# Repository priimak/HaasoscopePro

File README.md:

## HaasoscopePro

### An Affordable 2 GHz 3.2 GS/s 12 bit open-source open-hardware expandable USB oscilloscope

### [Available on CrowdSupply](https://www.crowdsupply.com/andy-haas/haasoscope-pro)

### [Hackaday.io Page](https://hackaday.io/project/200773-haasoscope-pro)

#### Schematics in PDF: [haasoscope_pro_adc_fpga_board_schematics.pdf](adc%20board%2Fhaasoscope_pro_adc_fpga_board_schematics.pdf)

#### Routing image: [haasoscope_pro_adc_fpga_board_routing.png](adc%20board%2Fhaasoscope_pro_adc_fpga_board_routing.png)

#### Firmware overview: [firmware schematic.pdf](adc%20board%20firmware/schematic.pdf)

### Quick start (Windows/Mac/Linux)

1) Plug Haasoscope Pro into your computer via USB C
2) Download code and unzip it: https://github.com/drandyhaas/HaasoscopePro/archive/refs/heads/main.zip
3) Run **HaasoscopeProQt** in the <code>HaasoscopePro/software/dist/(OS)_HaasoscopeProQt</code> directory

### Tips

- If not enough power is supplied or issues happen during readout, plug in via a powered USB hub, a USB-A to C cable, or use an external 12V power adapter
- If the board is not found on Linux, use this udev rule and then plug it in: <code>sudo cp HaasoscopePro/software/ft245.rules /etc/udev/rules.d/</code>
- If you get an error like "qt.qpa.plugin: Could not load the Qt platform plugin "xcb" in "" even though it was found", try: <code>sudo apt install libxcb-xinerama0</code>

### Fuller way of running

1) Install python3 and git (operating system dependent)
2) Install dependencies: <br><code>pip3 install numpy scipy pyqtgraph PyQt5 pyftdi ftd2xx</code>
3) Get code: <br><code>git clone https://github.com/drandyhaas/HaasoscopePro.git</code>
4) Install [FTDI D2xx driver](https://ftdichip.com/drivers/d2xx-drivers/)
<br>for Windows: install using the [setup exe](https://ftdichip.com/wp-content/uploads/2021/08/CDM212364_Setup.zip)
<br>for Mac can just do: <code>sudo cp HaasoscopePro/software/libftd2xx.dylib /usr/local/lib/</code> 
<br>for Linux can just do: <code>sudo cp HaasoscopePro/software/libftd2xx.so /usr/lib/</code>
5) Run:
<br><code>cd HaasoscopePro/software</code>
<br><code>python3 HaasoscopeProQt.py</code>
6) To remake exe for quick start:
<br><code>pip3 install pyinstaller</code> # install dependency once
<br><code>python3 -m PyInstaller HaasoscopeProQt.py</code>
<br><code>mv dist/HaasoscopeProQt dist/(OS)_HaasoscopeProQt</code>

### Repository structure

- [adc board](adc%20board/): Design files and documentation for the main board, based on Eagle 9.6.2
- [adc board/Kicad](adc%20board/Kicad): An import of the main board design files into KiCad 8
- [adc board firmware](adc%20board%20firmware/): Quartus lite project for the Altera Cyclone IV FPGA firmware (see [README](adc%20board%20firmware/README.md) in there for firmware upload instructions)
- [case](case/): Front and back PCB panels for the aluminum case
- [software](software/): Python files for the oscilloscope program
- [sub boards](sub%20boards/): Eagle design files and documentation for smaller test boards that were used during development 

### 2 GHz Active Probe

All designs for the accompanying active probe are in a separate [repository](https://github.com/drandyhaas/oshw-active-probe)

### Editing the GUI

The Haasoscope Pro GUI can be edited using [Qt Designer](https://www.pythonguis.com/installation/install-qt-designer-standalone/), started with:
<br><code>pip install pyqt5-tools</code>
<br><code>pyqt5-tools designer</code>
<br>Then open software/HaasoscopePro.ui or HaasoscopeProFFT.ui etc.

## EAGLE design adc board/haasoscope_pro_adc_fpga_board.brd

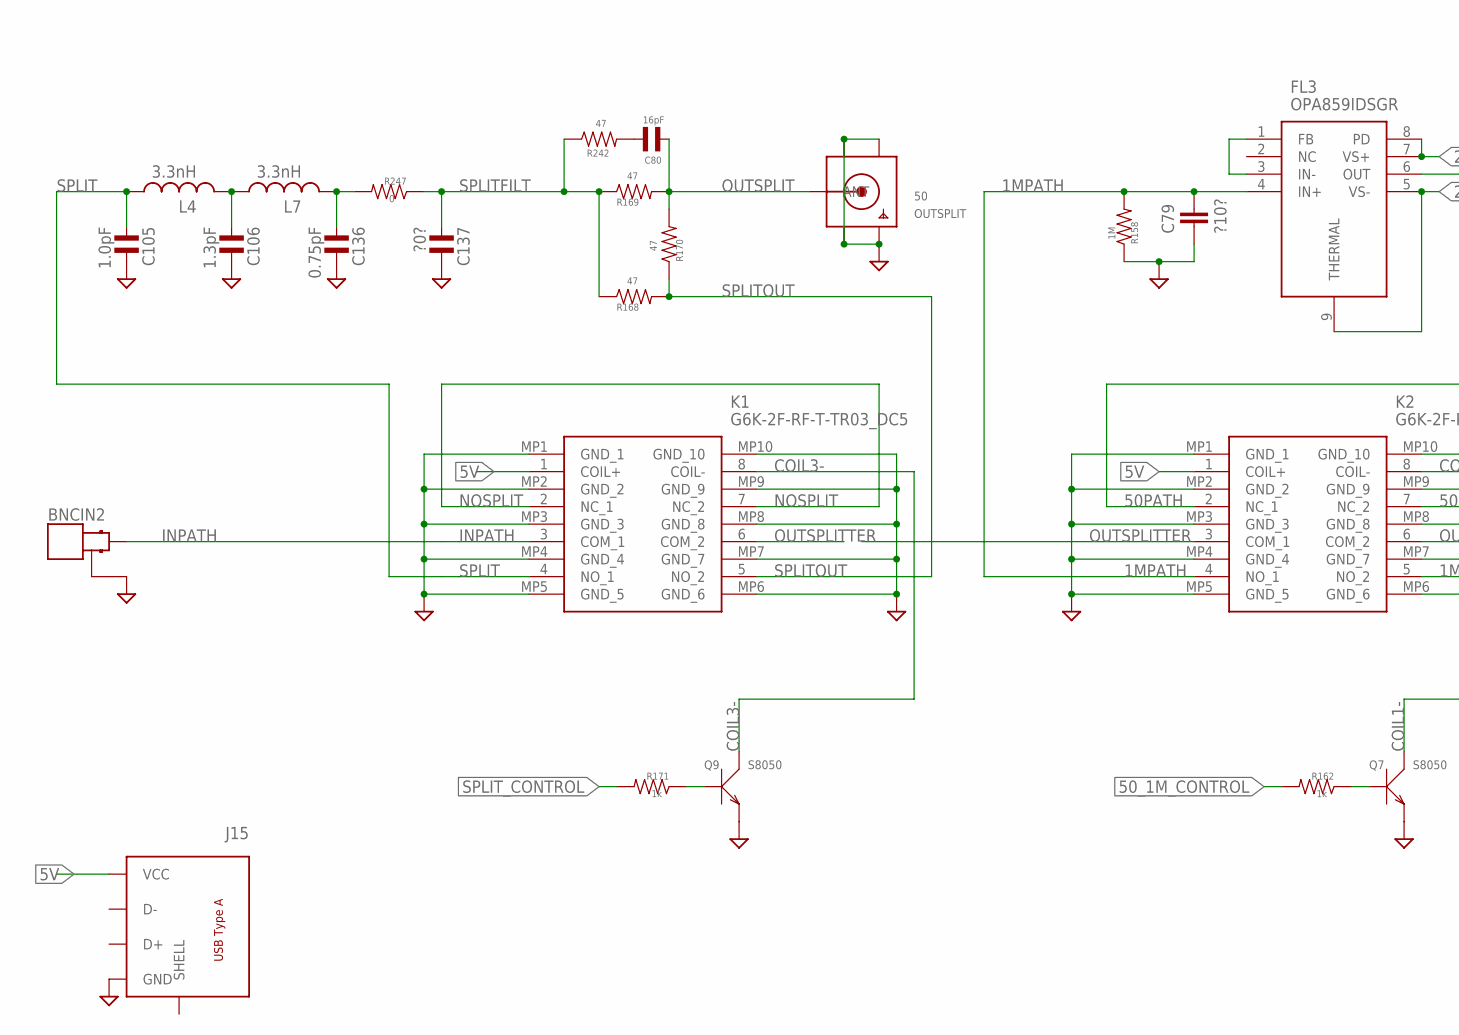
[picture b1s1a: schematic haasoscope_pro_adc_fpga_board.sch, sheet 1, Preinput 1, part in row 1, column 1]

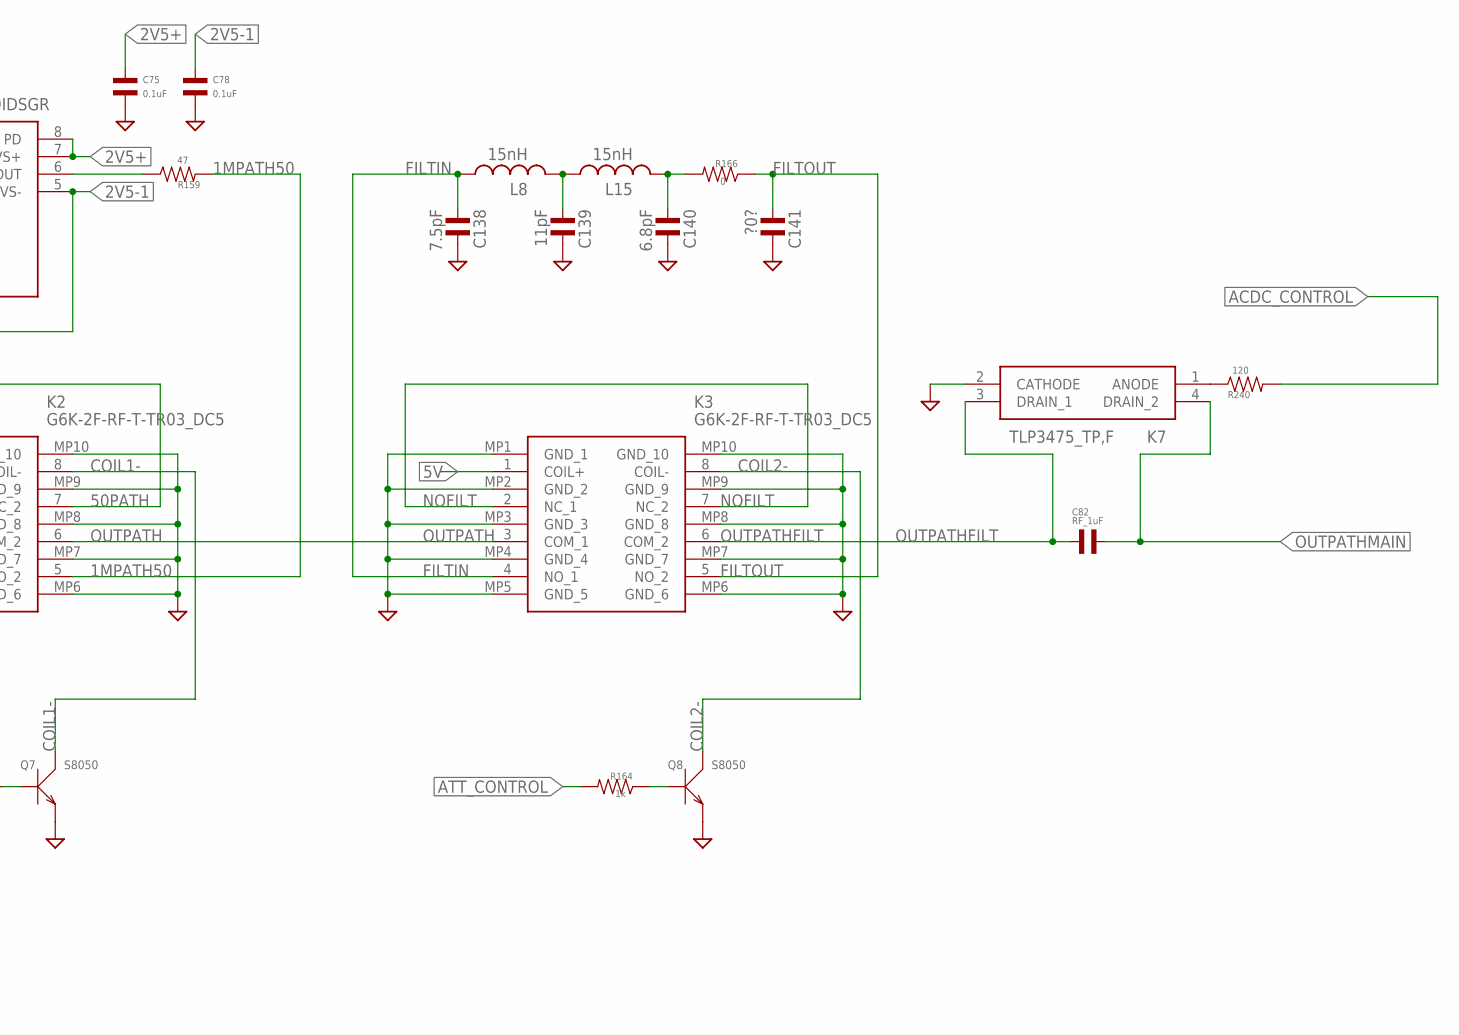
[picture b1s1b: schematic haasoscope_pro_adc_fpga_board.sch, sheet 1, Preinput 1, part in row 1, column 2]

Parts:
BNCIN2: MOLEX_BNC_73100-0105; MOLEX-BNC-73100-0105; MPN 73100-0105
C75, C78: 0.1uF; C0402
C79: ?10?; C0805
C80: 16pF; C0402
C82: RF_1uF; C0402; LCSC C52923
C105: 1.0pF; C0402
C106: 1.3pF; C0402
C136: 0.75pF; C0402
C137, C141: ?0?; C0402
C138: 7.5pF; C0402
C139: 11pF; C0402
C140: 6.8pF; C0402
FL3: OPA859IDSGR; SON50P200X200X80-9N
J15: test1; USB-2.0-A-THT-RA-TE_AMP-292303-1
K1, K2, K3: G6K-2F-RF-T-TR03_DC5; G6K2FRFTTR03DC5
K7: TLP3475_TP,F; TLP3475TPF; MANUFACTURER_PART_NUMBER TLP3475; MOUSER_PART_NUMBER 757-TLP3475
L4, L7: 3.3nH; RESC0402_N; LCSC C162542
L8, L15: 15nH; RESC0402_N; LCSC C521066
OUTSPLIT: 50; SMA_EDGELAUNCH
Q7, Q8, Q9: S8050; SOT-23; LCSC C7420370
R158: 1M; R0402
R159, R168, R169, R170, R242: 47; R0402
R162, R164, R171: 1k; R0402
R166, R247: 0; R0402
R240: 120; R0402

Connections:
1MPATH: C79.2, FL3.4 (IN+), K2.4 (NO_1), R158.P$2
1MPATH50: K2.5 (NO_2), R159.P$2
2V5+: C75.P$1, FL3.7 (VS+), FL3.8 (PD); also elsewhere on the board
2V5-1: C78.P$1, FL3.5 (VS-), FL3.9 (THERMAL); also elsewhere on the board
5V: J15.P$1 (VCC), K1.1 (COIL+), K2.1 (COIL+), K3.1 (COIL+); also elsewhere on the board
50PATH: K2.2 (NC_1), K2.7 (NC_2)
50_1M_CONTROL: R162.P$2; also elsewhere on the board
ACDC_CONTROL: R240.P$2; also elsewhere on the board
ATT_CONTROL: R164.P$2; also elsewhere on the board
COIL1-: K2.8 (COIL-), Q7.3 (C)
COIL2-: K3.8 (COIL-), Q8.3 (C)
COIL3-: K1.8 (COIL-), Q9.3 (C)
FILTIN: C138.P$1, K3.4 (NO_1), L8.1
FILTOUT: C141.P$1, K3.5 (NO_2), R166.P$1
GND: BNCIN2.GND1 (GND), BNCIN2.GND2 (GND), C75.P$2, C78.P$2, C79.1, C105.P$2, C106.P$2, C136.P$2, C137.P$2, C138.P$2, C139.P$2, C140.P$2, C141.P$2, J15.P$4 (GND), K1.MP1 (GND_1), K1.MP2 (GND_2), K1.MP3 (GND_3), K1.MP4 (GND_4), K1.MP5 (GND_5), K1.MP6 (GND_6), K1.MP7 (GND_7), K1.MP8 (GND_8), K1.MP9 (GND_9), K1.MP10 (GND_10), K2.MP1 (GND_1), K2.MP2 (GND_2), K2.MP3 (GND_3), K2.MP4 (GND_4), K2.MP5 (GND_5), K2.MP6 (GND_6), K2.MP7 (GND_7), K2.MP8 (GND_8), K2.MP9 (GND_9), K2.MP10 (GND_10), K3.MP1 (GND_1), K3.MP2 (GND_2), K3.MP3 (GND_3), K3.MP4 (GND_4), K3.MP5 (GND_5), K3.MP6 (GND_6), K3.MP7 (GND_7), K3.MP8 (GND_8), K3.MP9 (GND_9), K3.MP10 (GND_10), K7.2 (CATHODE), OUTSPLIT.GND@1 (GND4), OUTSPLIT.GND@2 (GND3), OUTSPLIT.GND@3 (GND2), OUTSPLIT.GND@4 (GND1), Q7.2 (E), Q8.2 (E), Q9.2 (E), R158.P$1; also elsewhere on the board
INPATH: BNCIN2.SIGNAL, K1.3 (COM_1)
unnamed: C139.P$1, L8.2, L15.1
unnamed: FL3.6 (OUT), R159.P$1
unnamed: FL3.1 (FB), FL3.3 (IN-)
unnamed: Q7.1 (B), R162.P$1
unnamed: Q8.1 (B), R164.P$1
unnamed: Q9.1 (B), R171.P$1
unnamed: K7.1 (ANODE), R240.P$1
unnamed: C80.P$1, R242.P$2
unnamed: C140.P$1, L15.2, R166.P$2
unnamed: C136.P$1, L7.2, R247.P$2
unnamed: C106.P$1, L4.2, L7.1
NOFILT: K3.2 (NC_1), K3.7 (NC_2)
NOSPLIT: K1.2 (NC_1), K1.7 (NC_2)
OUTPATH: K2.6 (COM_2), K3.3 (COM_1)
OUTPATHFILT: C82.P$1, K3.6 (COM_2), K7.3 (DRAIN_1)
OUTPATHMAIN: C82.P$2, K7.4 (DRAIN_2); also elsewhere on the board
OUTSPLIT: C80.P$2, OUTSPLIT.P (ANT), R169.P$2, R170.P$2
OUTSPLITTER: K1.6 (COM_2), K2.3 (COM_1)
SPLIT: C105.P$1, K1.4 (NO_1), L4.1
SPLITFILT: C137.P$1, R168.P$1, R169.P$1, R242.P$1, R247.P$1
SPLITOUT: K1.5 (NO_2), R168.P$2, R170.P$1
SPLIT_CONTROL: R171.P$2; also elsewhere on the board

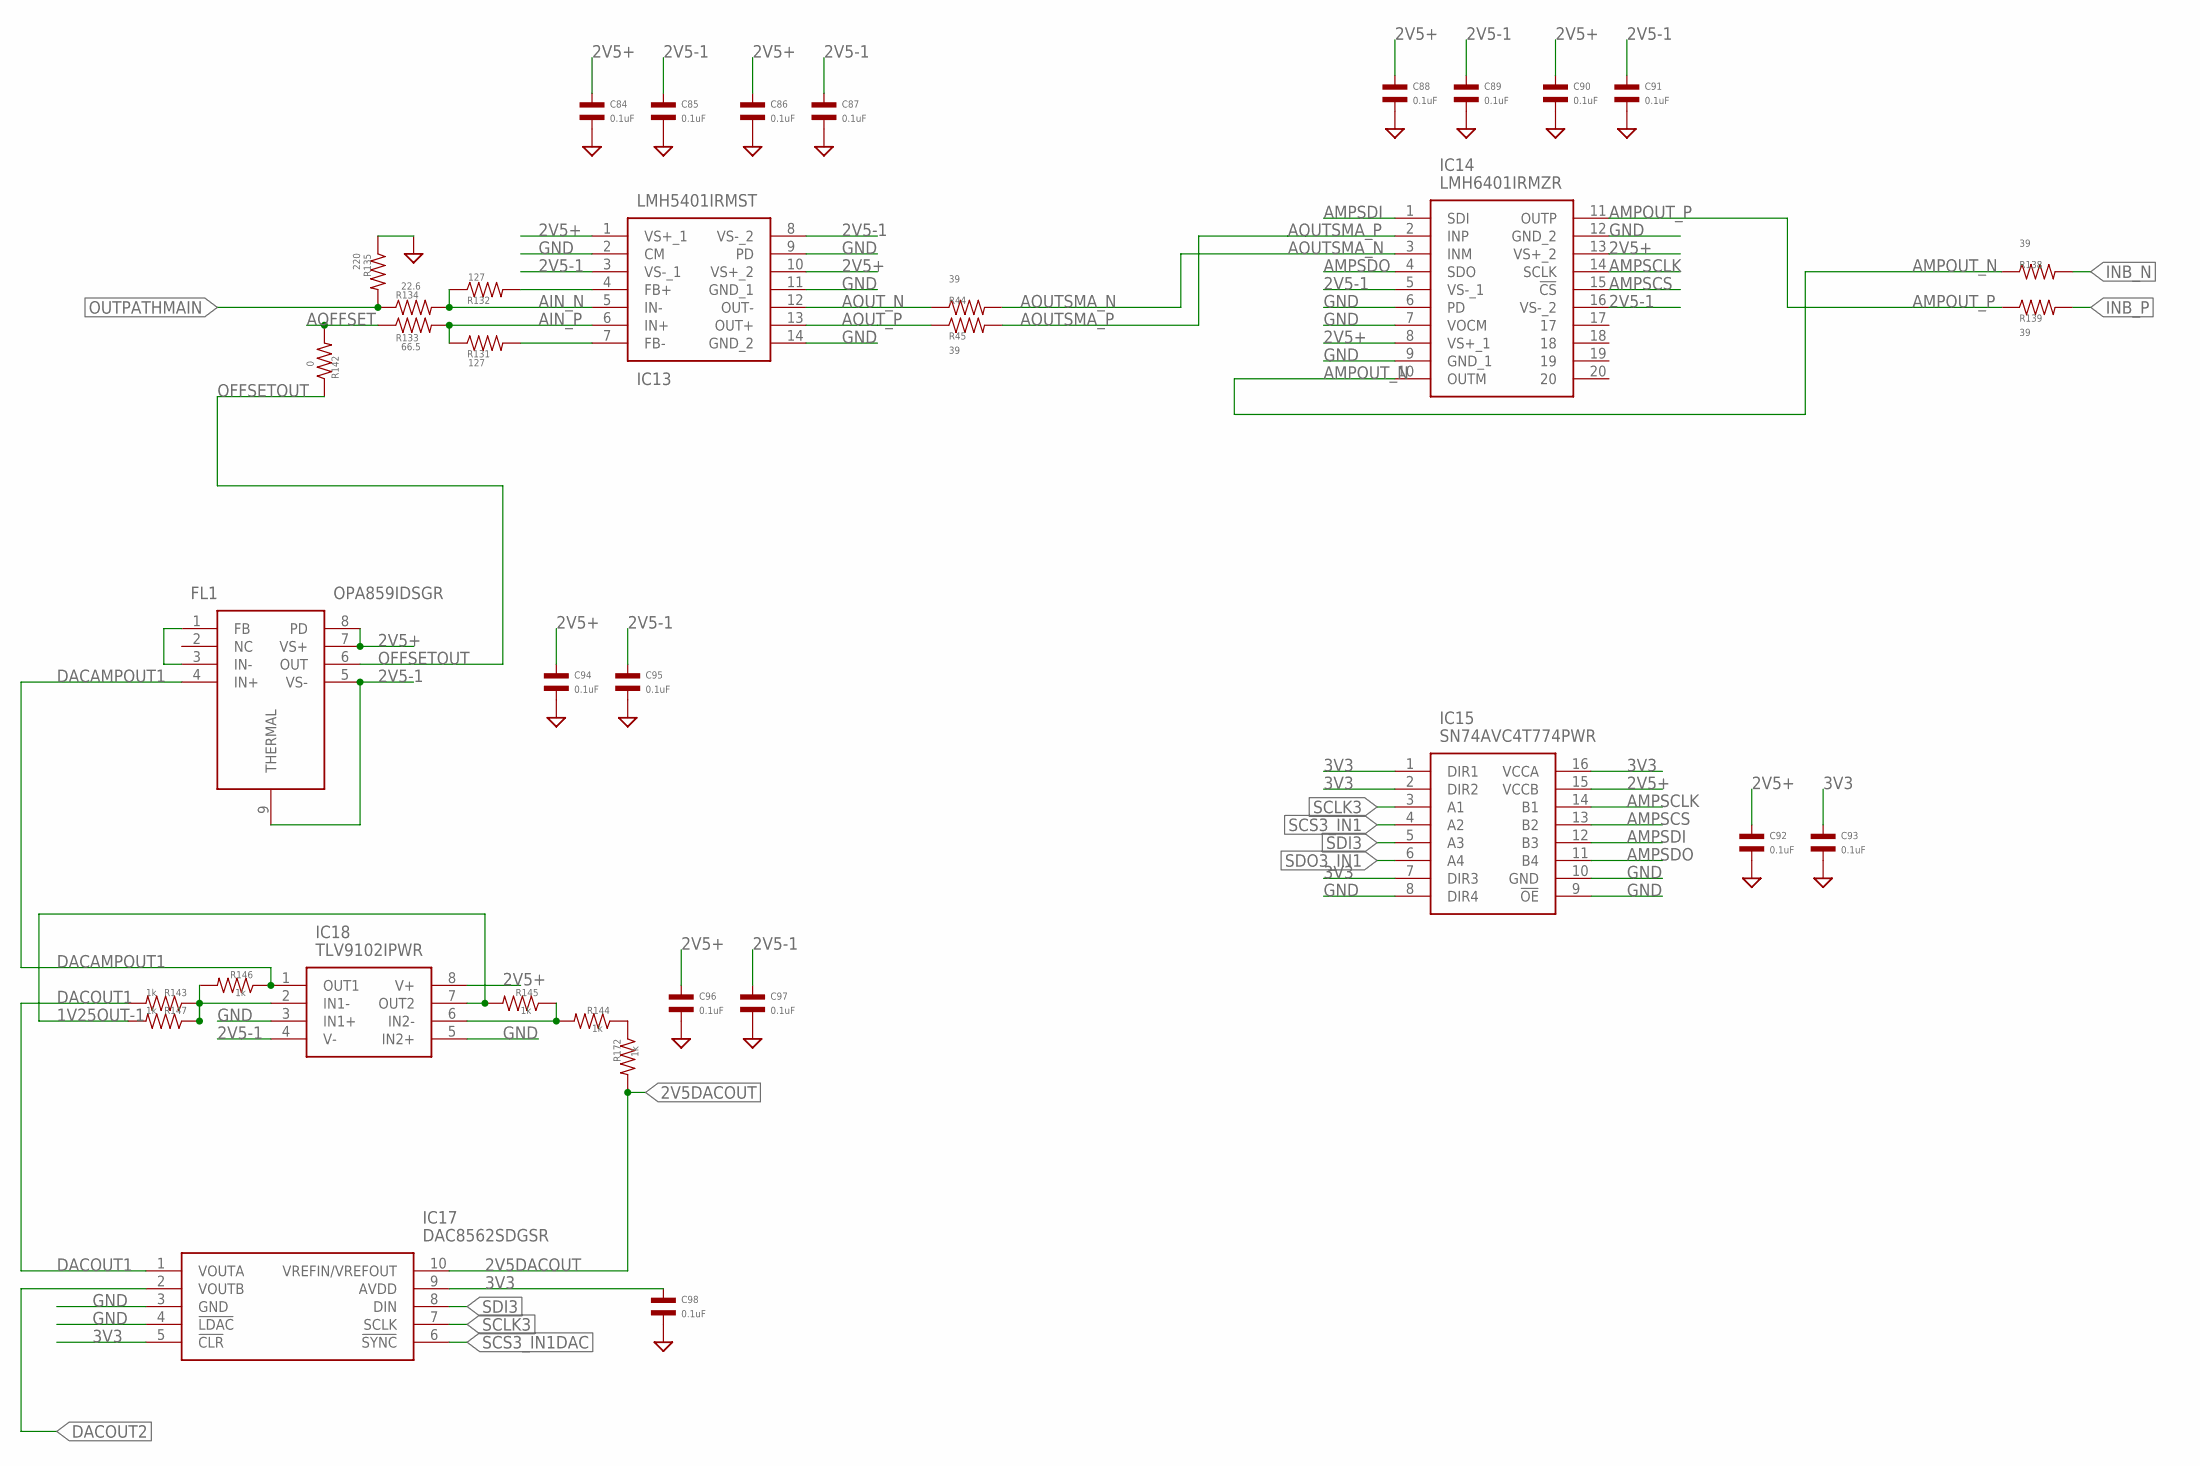
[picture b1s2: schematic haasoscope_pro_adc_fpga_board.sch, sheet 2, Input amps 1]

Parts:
C84, C85, C86, C87, C88, C89, C90, C91, C92, C93, C94, C95, C96, C97, C98: 0.1uF; C0402
FL1: OPA859IDSGR; SON50P200X200X80-9N
IC13: LMH5401IRMST; LMH5401IRMSR
IC14: LMH6401IRMZR
IC15: SN74AVC4T774PWR; SOP65P640X120-16N
IC17: DAC8562SDGSR; SOP50P490X110-10N
IC18: TLV9102IPWR; SOP65P640X120-8N
R44, R45, R138, R139: 39; R0402
R131, R132: 127; R0402
R133: 66.5; R0402
R134: 22.6; R0402
R135: 220; R0402
R142: 0; R0402
R143, R144, R145, R146, R147, R172: 1k; R0402

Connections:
1V25OUT-1: IC18.7 (OUT2), R145.P$2, R147.P$2
2V5+: C84.P$1, C86.P$1, C88.P$1, C90.P$1, C92.P$1, C94.P$1, C96.P$1, FL1.7 (VS+), FL1.8 (PD), IC13.1 (VS+_1), IC13.10 (VS+_2), IC14.8 (VS+_1), IC14.13 (VS+_2), IC15.15 (VCCB), IC18.8 (V+); also elsewhere on the board
2V5-1: C85.P$1, C87.P$1, C89.P$1, C91.P$1, C95.P$1, C97.P$1, FL1.5 (VS-), FL1.9 (THERMAL), IC13.3 (VS-_1), IC13.8 (VS-_2), IC14.5 (VS-_1), IC14.16 (VS-_2), IC18.4 (V-); also elsewhere on the board
2V5DACOUT: IC17.10 (VREFIN/VREFOUT), R172.P$2; also elsewhere on the board
3V3: C93.P$1, C98.P$1, IC15.1 (DIR1), IC15.2 (DIR2), IC15.7 (DIR3), IC15.16 (VCCA), IC17.5 (!CLR), IC17.9 (AVDD); also elsewhere on the board
AIN_N: IC13.5 (IN-), R132.P$1, R134.P$2
AIN_P: IC13.6 (IN+), R131.P$1, R133.P$2
AMPOUT_N: IC14.10 (OUTM), R138.P$1
AMPOUT_P: IC14.11 (OUTP), R139.P$1
AMPSCLK: IC14.14 (SCLK), IC15.14 (B1)
AMPSCS: IC14.15 (!CS), IC15.13 (B2)
AMPSDI: IC14.1 (SDI), IC15.12 (B3)
AMPSDO: IC14.4 (SDO), IC15.11 (B4)
AOFFSET: R133.P$1, R142.P$2
AOUTSMA_N: IC14.3 (INM), R44.P$2
AOUTSMA_P: IC14.2 (INP), R45.P$2
AOUT_N: IC13.12 (OUT-), R44.P$1
AOUT_P: IC13.13 (OUT+), R45.P$1
DACAMPOUT1: FL1.4 (IN+), IC18.1 (OUT1), R146.P$1
DACOUT1: IC17.1 (VOUTA), R143.P$2
DACOUT2: IC17.2 (VOUTB); also elsewhere on the board
GND: C84.P$2, C85.P$2, C86.P$2, C87.P$2, C88.P$2, C89.P$2, C90.P$2, C91.P$2, C92.P$2, C93.P$2, C94.P$2, C95.P$2, C96.P$2, C97.P$2, C98.P$2, IC13.2 (CM), IC13.9 (PD), IC13.11 (GND_1), IC13.14 (GND_2), IC14.6 (PD), IC14.7 (VOCM), IC14.9 (GND_1), IC14.12 (GND_2), IC15.8 (DIR4), IC15.9 (!OE), IC15.10 (GND), IC17.3 (GND), IC17.4 (!LDAC), IC18.3 (IN1+), IC18.5 (IN2+), R135.P$1; also elsewhere on the board
INB_N: R138.P$2; also elsewhere on the board
INB_P: R139.P$2; also elsewhere on the board
unnamed: FL1.1 (FB), FL1.3 (IN-)
unnamed: IC13.7 (FB-), R131.P$2
unnamed: IC13.4 (FB+), R132.P$2
unnamed: IC18.6 (IN2-), R144.P$2, R145.P$1
unnamed: IC18.2 (IN1-), R143.P$1, R146.P$2, R147.P$1
unnamed: R144.P$1, R172.P$1
OFFSETOUT: FL1.6 (OUT), R142.P$1
OUTPATHMAIN: R134.P$1, R135.P$2; also elsewhere on the board
SCLK3: IC15.3 (A1), IC17.7 (SCLK); also elsewhere on the board
SCS3_IN1: IC15.4 (A2); also elsewhere on the board
SCS3_IN1DAC: IC17.6 (!SYNC); also elsewhere on the board
SDI3: IC15.5 (A3), IC17.8 (DIN); also elsewhere on the board
SDO3_IN1: IC15.6 (A4); also elsewhere on the board

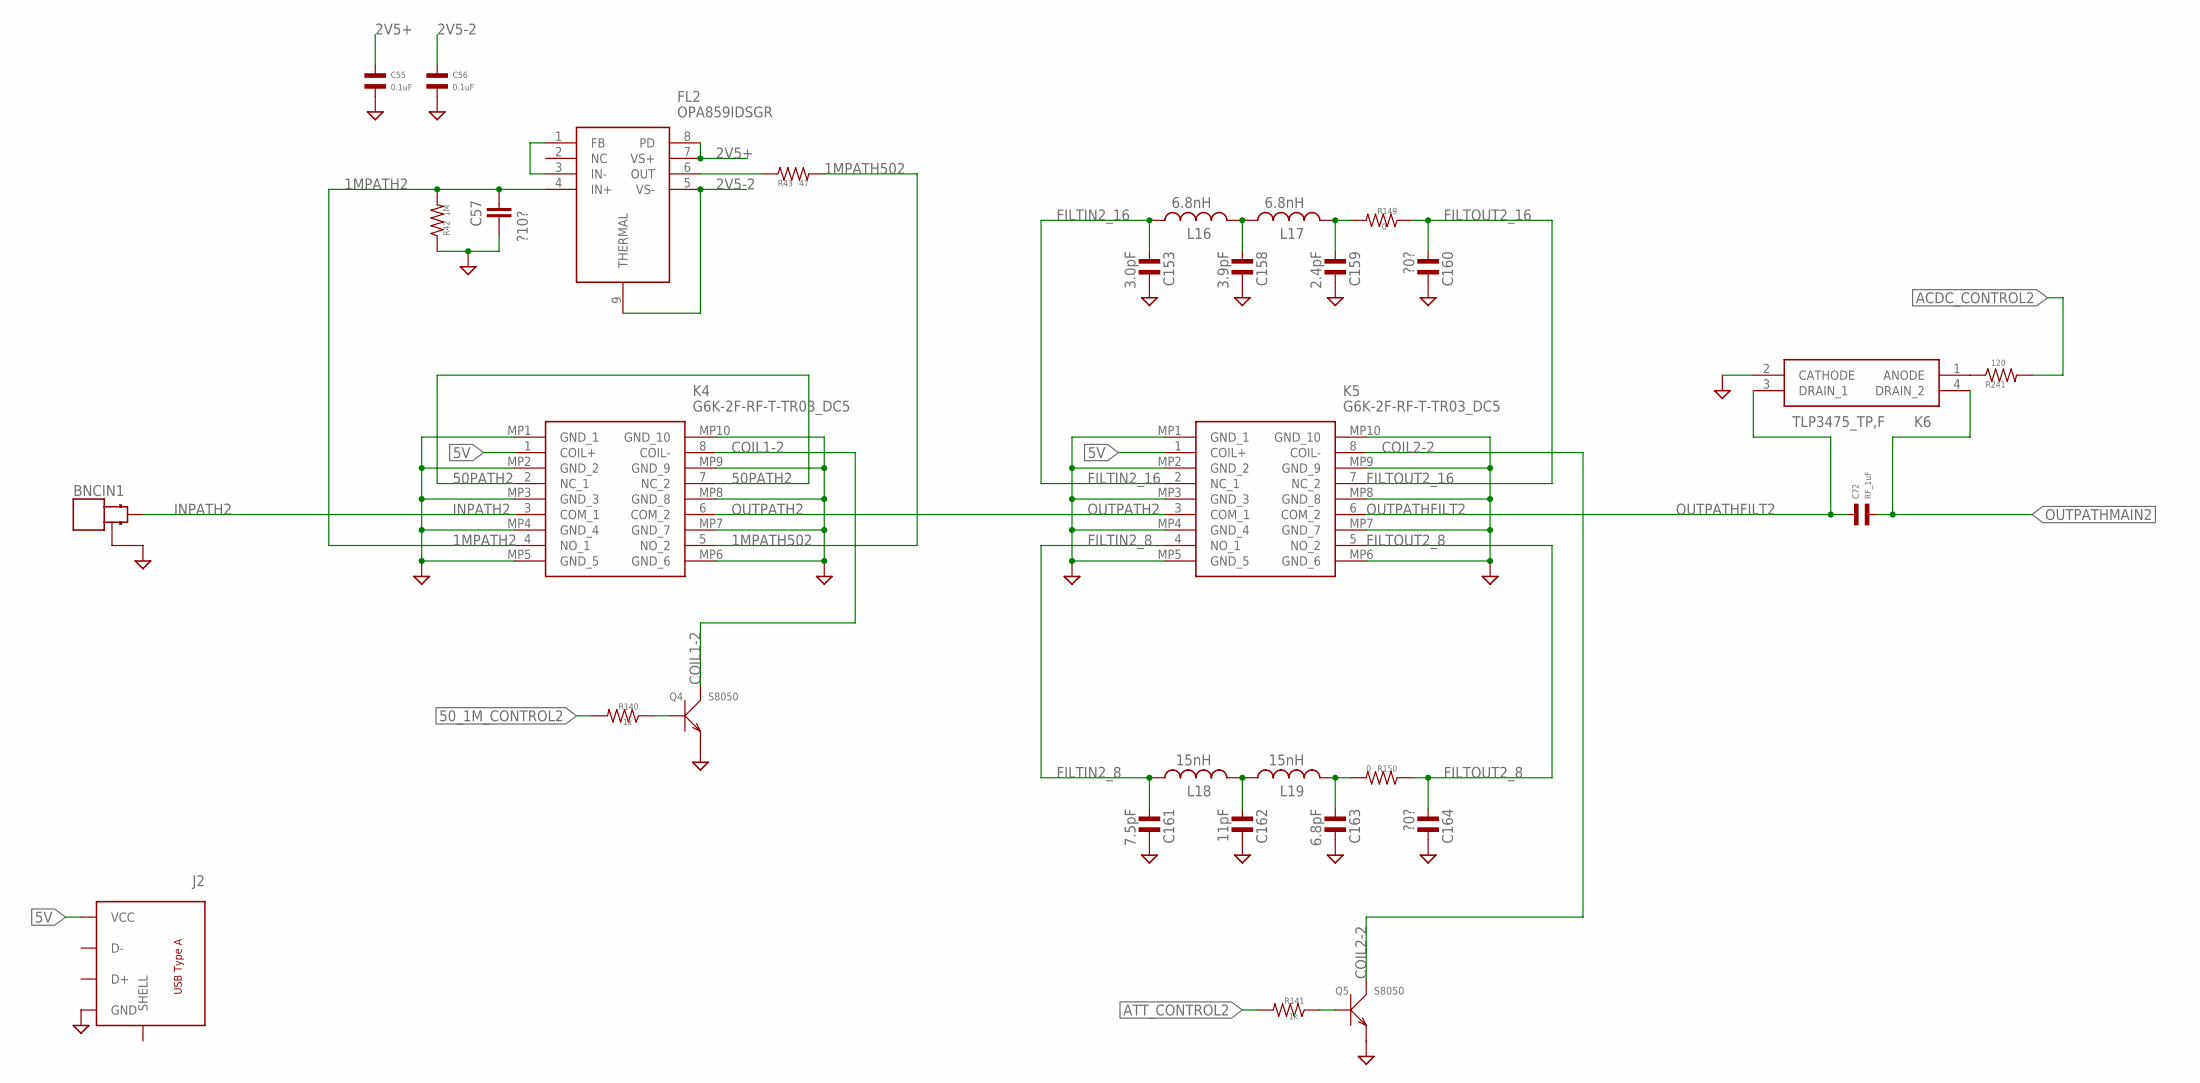
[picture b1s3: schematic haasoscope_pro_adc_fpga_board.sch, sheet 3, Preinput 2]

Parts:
BNCIN1: MOLEX_BNC_73100-0105; MOLEX-BNC-73100-0105; MPN 73100-0105
C55, C56: 0.1uF; C0402
C57: ?10?; C0805
C72: RF_1uF; C0402; LCSC C52923
C153: 3.0pF; C0402
C158: 3.9pF; C0402
C159: 2.4pF; C0402
C160, C164: ?0?; C0402
C161: 7.5pF; C0402
C162: 11pF; C0402
C163: 6.8pF; C0402
FL2: OPA859IDSGR; SON50P200X200X80-9N
J2: test1; USB-2.0-A-THT-RA-TE_AMP-292303-1
K4, K5: G6K-2F-RF-T-TR03_DC5; G6K2FRFTTR03DC5
K6: TLP3475_TP,F; TLP3475TPF; MANUFACTURER_PART_NUMBER TLP3475; MOUSER_PART_NUMBER 757-TLP3475
L16, L17: 6.8nH; RESC0402_N; LCSC C77110
L18, L19: 15nH; RESC0402_N; LCSC C521066
Q4, Q5: S8050; SOT-23; LCSC C7420370
R42: 1M; R0402
R43: 47; R0402
R140, R141: 1k; R0402
R149, R150: 0; R0402
R241: 120; R0402

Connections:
1MPATH2: C57.2, FL2.4 (IN+), K4.4 (NO_1), R42.P$2
1MPATH502: K4.5 (NO_2), R43.P$2
2V5+: C55.P$1, FL2.7 (VS+), FL2.8 (PD); also elsewhere on the board
2V5-2: C56.P$1, FL2.5 (VS-), FL2.9 (THERMAL); also elsewhere on the board
5V: J2.P$1 (VCC), K4.1 (COIL+), K5.1 (COIL+); also elsewhere on the board
50PATH2: K4.2 (NC_1), K4.7 (NC_2)
50_1M_CONTROL2: R140.P$2; also elsewhere on the board
ACDC_CONTROL2: R241.P$2; also elsewhere on the board
ATT_CONTROL2: R141.P$2; also elsewhere on the board
COIL1-2: K4.8 (COIL-), Q4.3 (C)
COIL2-2: K5.8 (COIL-), Q5.3 (C)
FILTIN2_8: C161.P$1, K5.4 (NO_1), L18.1
FILTIN2_16: C153.P$1, K5.2 (NC_1), L16.1
FILTOUT2_8: C164.P$1, K5.5 (NO_2), R150.P$1
FILTOUT2_16: C160.P$1, K5.7 (NC_2), R149.P$1
GND: BNCIN1.GND1 (GND), BNCIN1.GND2 (GND), C55.P$2, C56.P$2, C57.1, C153.P$2, C158.P$2, C159.P$2, C160.P$2, C161.P$2, C162.P$2, C163.P$2, C164.P$2, J2.P$4 (GND), K4.MP1 (GND_1), K4.MP2 (GND_2), K4.MP3 (GND_3), K4.MP4 (GND_4), K4.MP5 (GND_5), K4.MP6 (GND_6), K4.MP7 (GND_7), K4.MP8 (GND_8), K4.MP9 (GND_9), K4.MP10 (GND_10), K5.MP1 (GND_1), K5.MP2 (GND_2), K5.MP3 (GND_3), K5.MP4 (GND_4), K5.MP5 (GND_5), K5.MP6 (GND_6), K5.MP7 (GND_7), K5.MP8 (GND_8), K5.MP9 (GND_9), K5.MP10 (GND_10), K6.2 (CATHODE), Q4.2 (E), Q5.2 (E), R42.P$1; also elsewhere on the board
INPATH2: BNCIN1.SIGNAL, K4.3 (COM_1)
unnamed: FL2.6 (OUT), R43.P$1
unnamed: FL2.1 (FB), FL2.3 (IN-)
unnamed: Q4.1 (B), R140.P$1
unnamed: Q5.1 (B), R141.P$1
unnamed: K6.1 (ANODE), R241.P$1
unnamed: C158.P$1, L16.2, L17.1
unnamed: C159.P$1, L17.2, R149.P$2
unnamed: C162.P$1, L18.2, L19.1
unnamed: C163.P$1, L19.2, R150.P$2
OUTPATH2: K4.6 (COM_2), K5.3 (COM_1)
OUTPATHFILT2: C72.P$1, K5.6 (COM_2), K6.3 (DRAIN_1)
OUTPATHMAIN2: C72.P$2, K6.4 (DRAIN_2); also elsewhere on the board

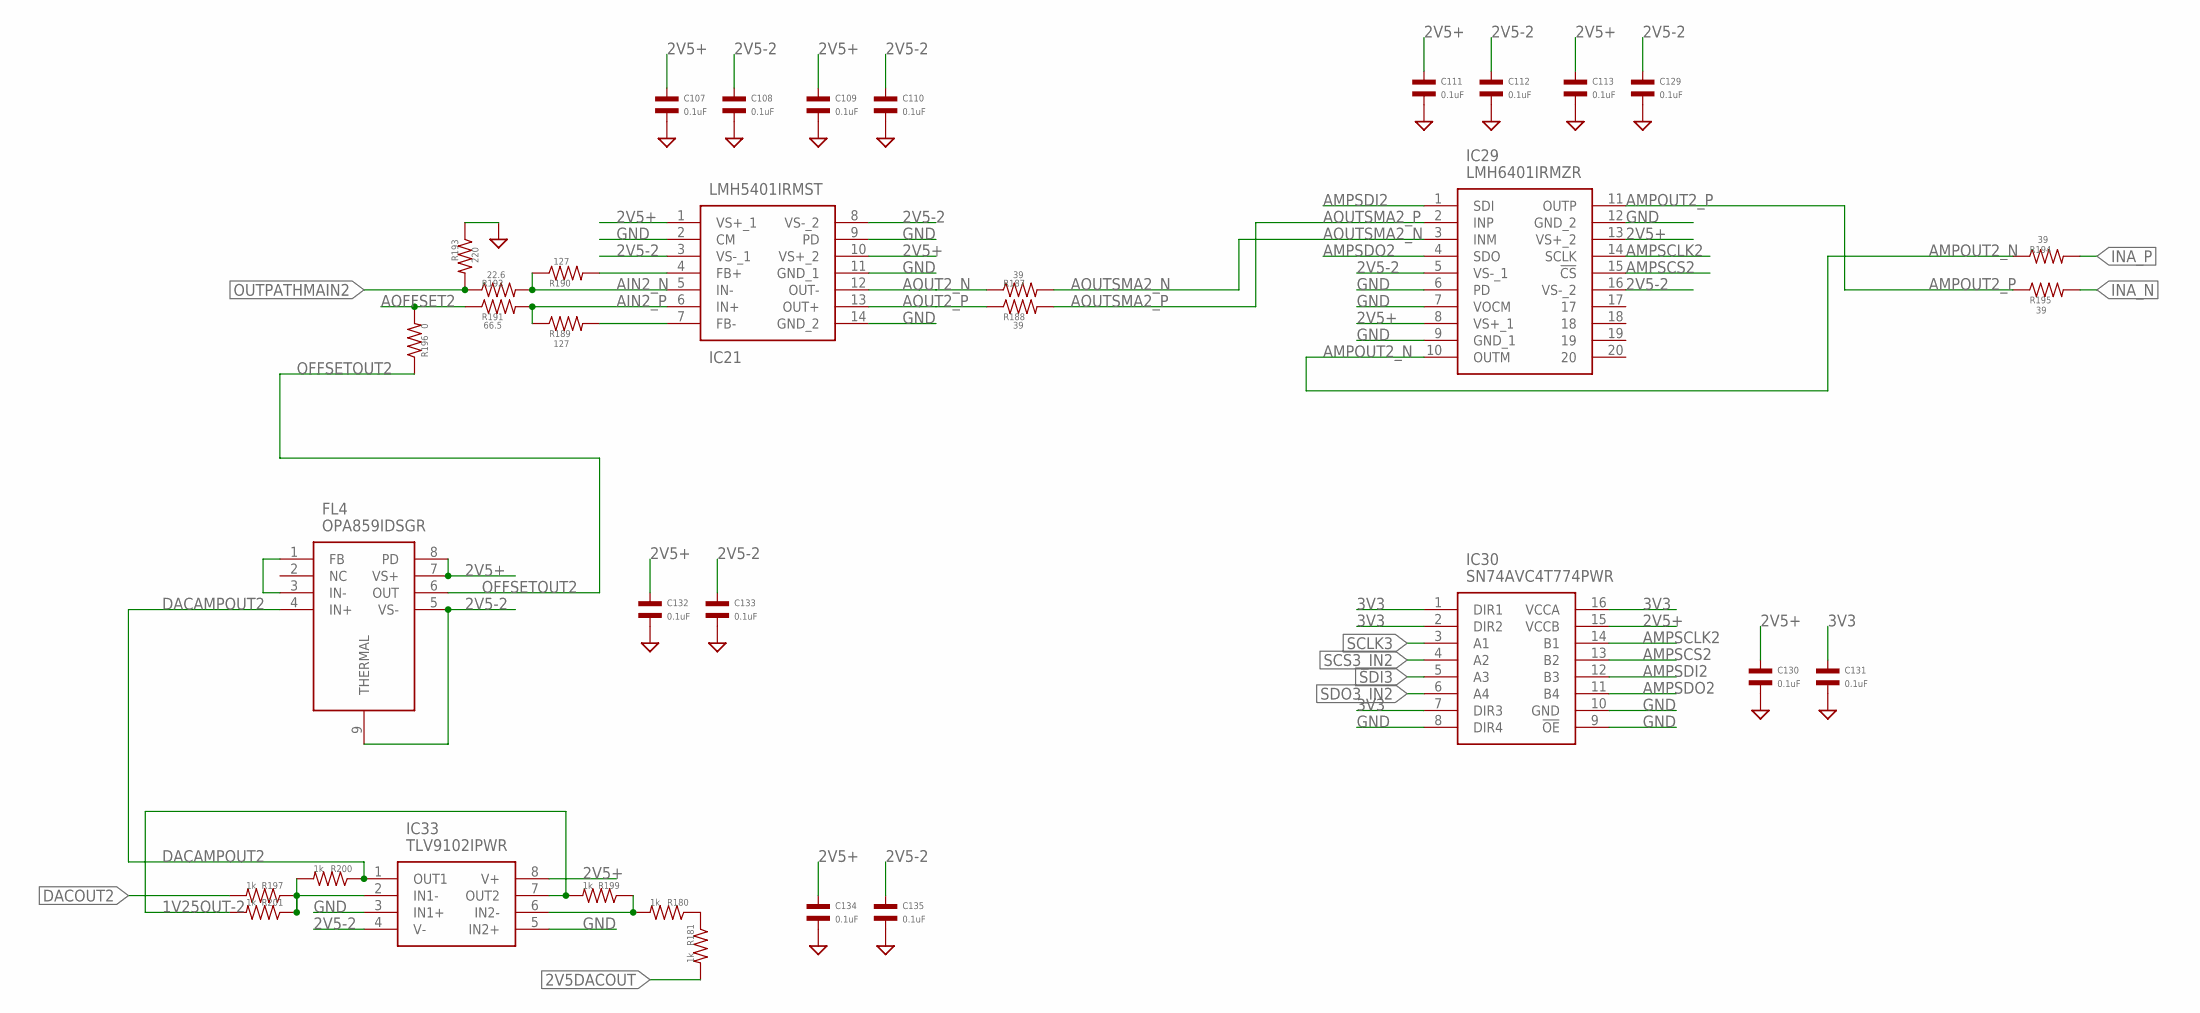
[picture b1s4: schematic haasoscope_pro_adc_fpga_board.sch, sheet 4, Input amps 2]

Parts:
C107, C108, C109, C110, C111, C112, C113, C129, C130, C131, C132, C133, C134, C135: 0.1uF; C0402
FL4: OPA859IDSGR; SON50P200X200X80-9N
IC21: LMH5401IRMST; LMH5401IRMSR
IC29: LMH6401IRMZR
IC30: SN74AVC4T774PWR; SOP65P640X120-16N
IC33: TLV9102IPWR; SOP65P640X120-8N
R180, R181, R197, R199, R200, R201: 1k; R0402
R187, R188, R194, R195: 39; R0402
R189, R190: 127; R0402
R191: 66.5; R0402
R192: 22.6; R0402
R193: 220; R0402
R196: 0; R0402

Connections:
1V25OUT-2: IC33.7 (OUT2), R199.P$2, R201.P$2
2V5+: C107.P$1, C109.P$1, C111.P$1, C113.P$1, C130.P$1, C132.P$1, C134.P$1, FL4.7 (VS+), FL4.8 (PD), IC21.1 (VS+_1), IC21.10 (VS+_2), IC29.8 (VS+_1), IC29.13 (VS+_2), IC30.15 (VCCB), IC33.8 (V+); also elsewhere on the board
2V5-2: C108.P$1, C110.P$1, C112.P$1, C129.P$1, C133.P$1, C135.P$1, FL4.5 (VS-), FL4.9 (THERMAL), IC21.3 (VS-_1), IC21.8 (VS-_2), IC29.5 (VS-_1), IC29.16 (VS-_2), IC33.4 (V-); also elsewhere on the board
2V5DACOUT: R181.P$2; also elsewhere on the board
3V3: C131.P$1, IC30.1 (DIR1), IC30.2 (DIR2), IC30.7 (DIR3), IC30.16 (VCCA); also elsewhere on the board
AIN2_N: IC21.5 (IN-), R190.P$1, R192.P$2
AIN2_P: IC21.6 (IN+), R189.P$1, R191.P$2
AMPOUT2_N: IC29.10 (OUTM), R194.P$1
AMPOUT2_P: IC29.11 (OUTP), R195.P$1
AMPSCLK2: IC29.14 (SCLK), IC30.14 (B1)
AMPSCS2: IC29.15 (!CS), IC30.13 (B2)
AMPSDI2: IC29.1 (SDI), IC30.12 (B3)
AMPSDO2: IC29.4 (SDO), IC30.11 (B4)
AOFFSET2: R191.P$1, R196.P$2
AOUT2_N: IC21.12 (OUT-), R187.P$1
AOUT2_P: IC21.13 (OUT+), R188.P$1
AOUTSMA2_N: IC29.3 (INM), R187.P$2
AOUTSMA2_P: IC29.2 (INP), R188.P$2
DACAMPOUT2: FL4.4 (IN+), IC33.1 (OUT1), R200.P$1
DACOUT2: R197.P$2; also elsewhere on the board
GND: C107.P$2, C108.P$2, C109.P$2, C110.P$2, C111.P$2, C112.P$2, C113.P$2, C129.P$2, C130.P$2, C131.P$2, C132.P$2, C133.P$2, C134.P$2, C135.P$2, IC21.2 (CM), IC21.9 (PD), IC21.11 (GND_1), IC21.14 (GND_2), IC29.6 (PD), IC29.7 (VOCM), IC29.9 (GND_1), IC29.12 (GND_2), IC30.8 (DIR4), IC30.9 (!OE), IC30.10 (GND), IC33.3 (IN1+), IC33.5 (IN2+), R193.P$1; also elsewhere on the board
INA_N: R195.P$2; also elsewhere on the board
INA_P: R194.P$2; also elsewhere on the board
unnamed: FL4.1 (FB), FL4.3 (IN-)
unnamed: IC21.7 (FB-), R189.P$2
unnamed: IC21.4 (FB+), R190.P$2
unnamed: IC33.6 (IN2-), R180.P$2, R199.P$1
unnamed: IC33.2 (IN1-), R197.P$1, R200.P$2, R201.P$1
unnamed: R180.P$1, R181.P$1
OFFSETOUT2: FL4.6 (OUT), R196.P$1
OUTPATHMAIN2: R192.P$1, R193.P$2; also elsewhere on the board
SCLK3: IC30.3 (A1); also elsewhere on the board
SCS3_IN2: IC30.4 (A2); also elsewhere on the board
SDI3: IC30.5 (A3); also elsewhere on the board
SDO3_IN2: IC30.6 (A4); also elsewhere on the board

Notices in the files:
parts and their libraries:
SparkFun-Connectors: Licensing: Creative Commons ShareAlike 4.0 International - https://creativecommons.org/licenses/by-sa/4.0
microbuilder: This work is placed in the public domain, and may be freely used for commercial and non-commercial work with the following conditions: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
